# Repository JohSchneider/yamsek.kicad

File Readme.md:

Find build documentation at the Hackaday.io site for [Yet another Modular split ergonomic Keyboard](https://hackaday.io/project/21164-yamsek)

A reversible PCB for three-quarts of the keyboard matrix, with the remaining quarter being a handwired thumbcluster.

The design "fully embraces" I2C as interconnect:
- an io expander handles the matrix, the three matrix rows on the pcb, as well as the additional row in the thumbcluster
- along the edge are three places where a ribbon cable can be soldered to to connect to the next module
- "modules" are the main mcu running QMK, two of these pcbs and additional sensors (e.g. an I2C touchpad, ... )

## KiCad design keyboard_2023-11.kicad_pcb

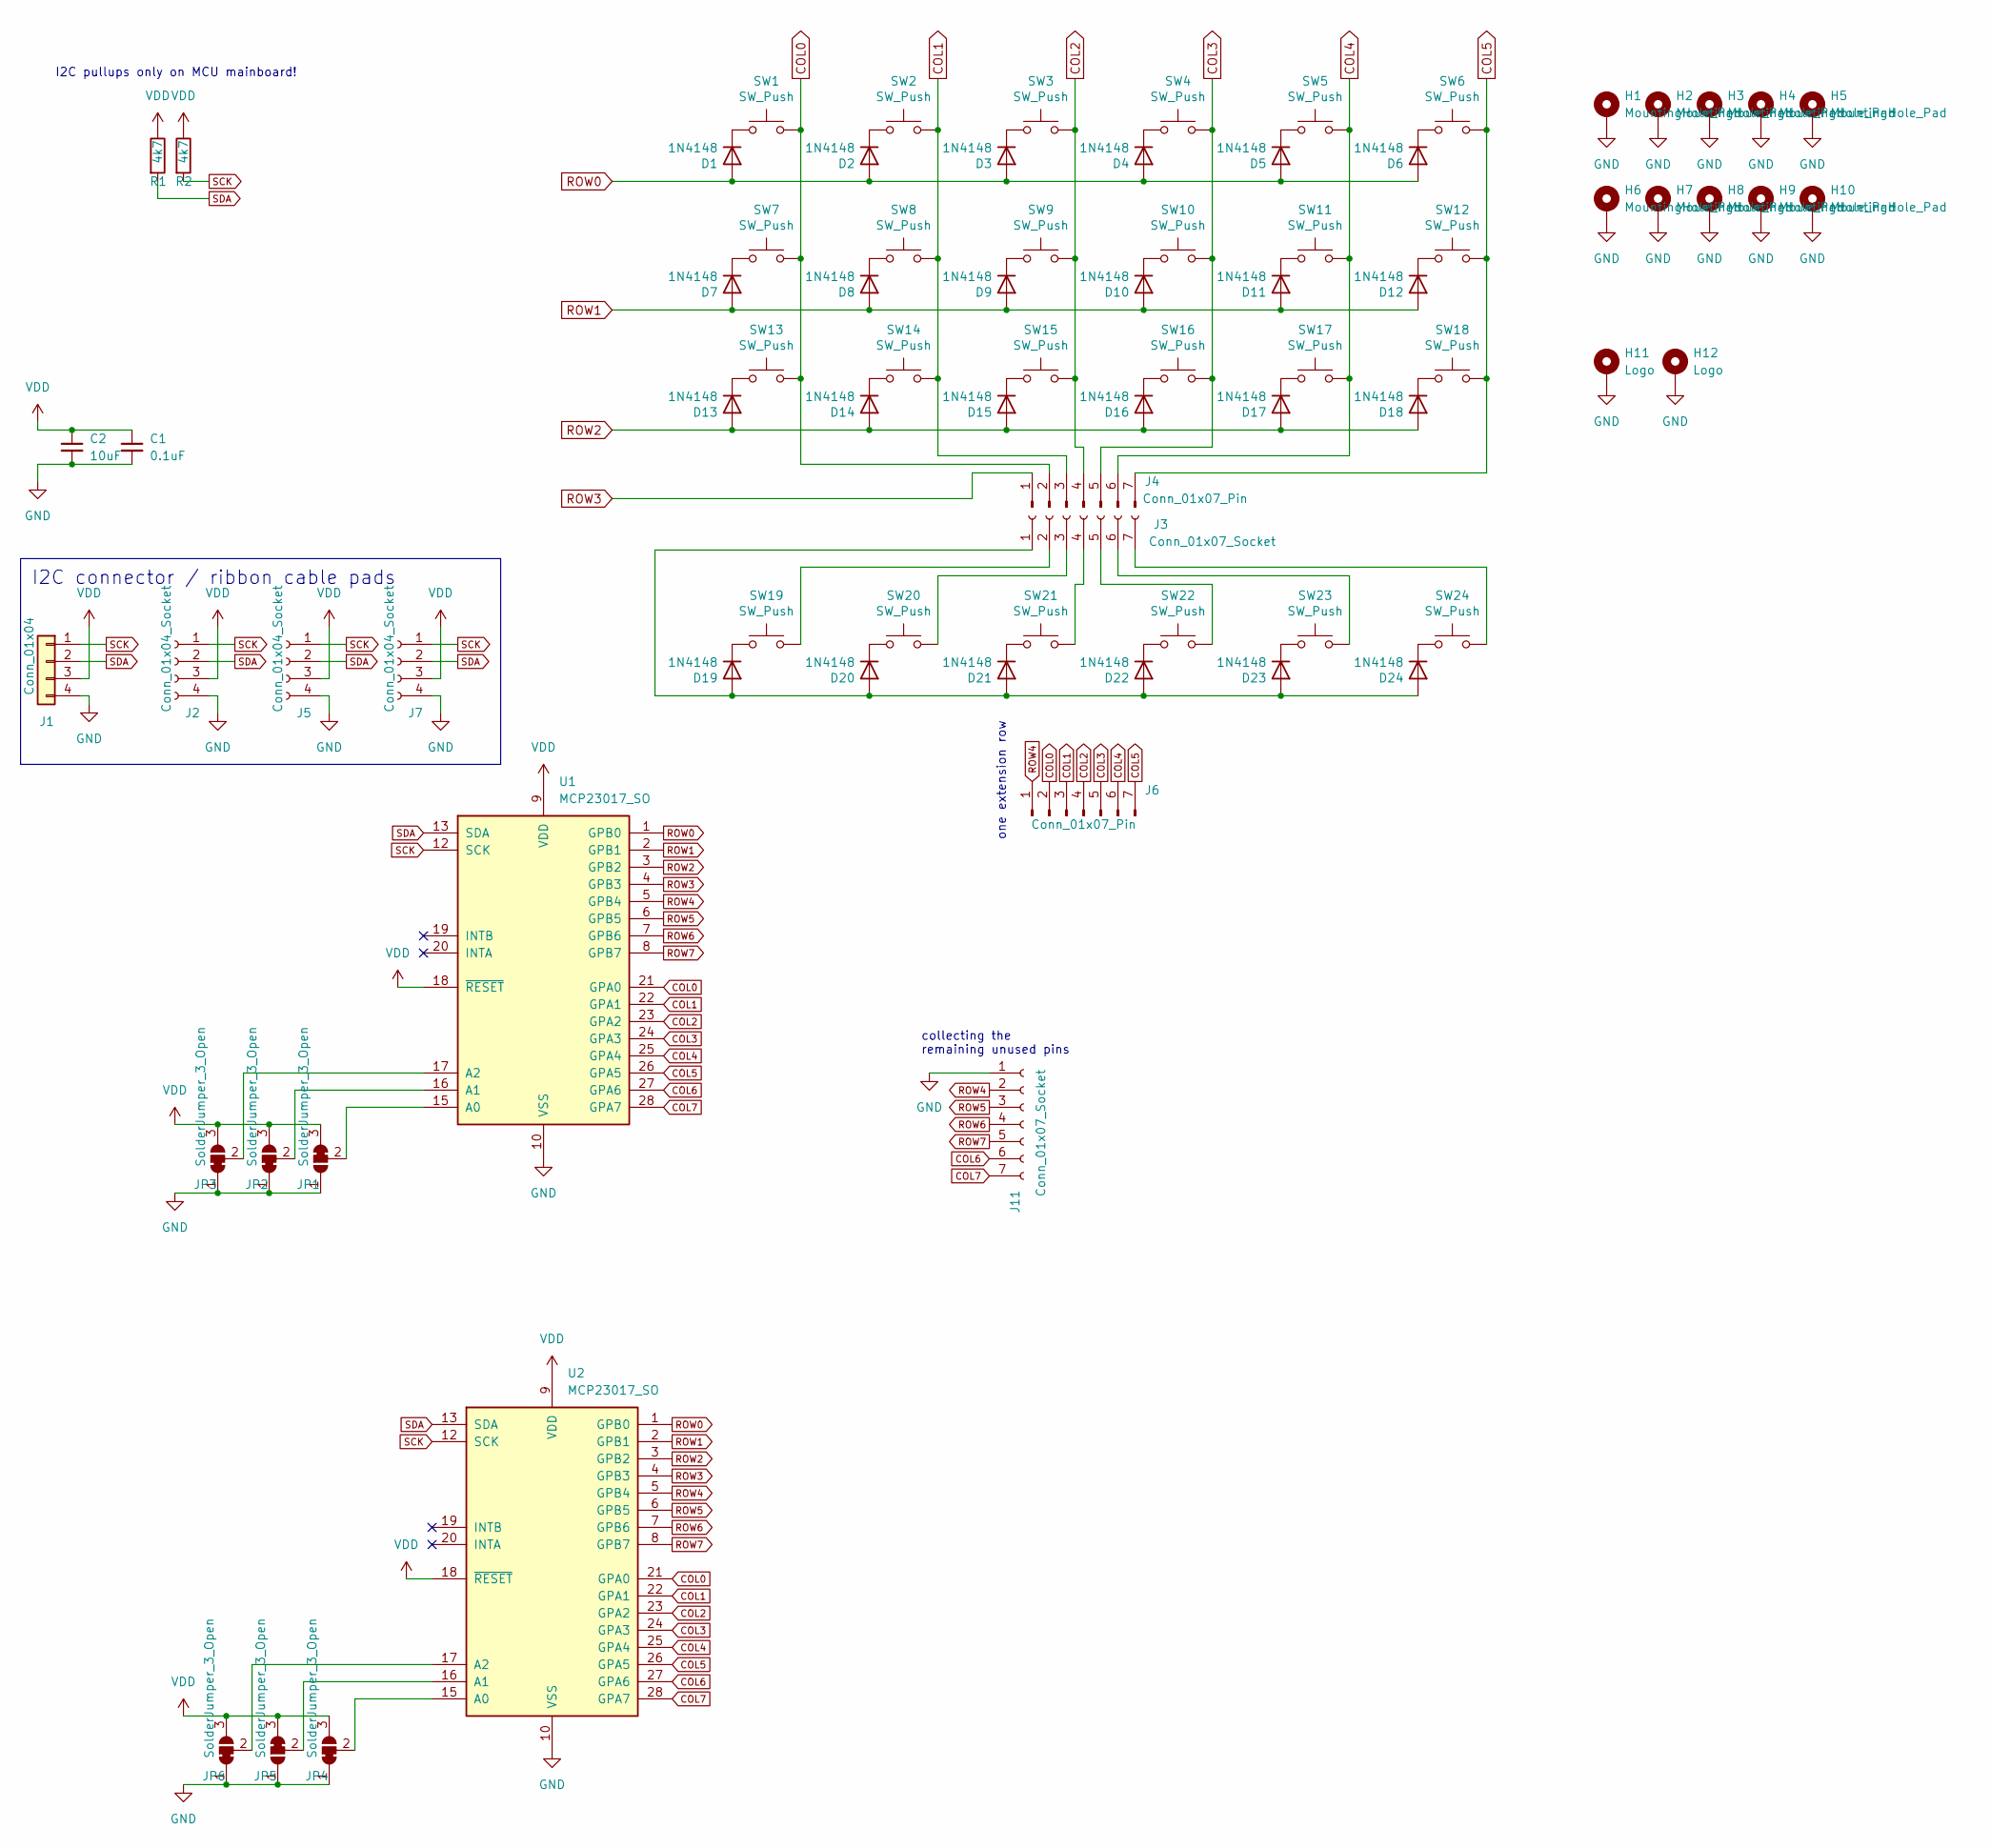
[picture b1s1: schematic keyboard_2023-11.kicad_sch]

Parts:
C1: 0.1uF; C-0805_2012Metric
C2: 10uF; C-0805_2012Metric
D1, D2, D3, D4, D5, D6, D7, D8, D9, D10, D11, D12, D13, D14, D15, D16, D17, D18, D19, D20, D21, D22, D23, D24: 1N4148; D_SOD-123
H1, H2, H3, H4, H5, H6, H7, H8, H9, H10: MountingHole_Pad; MountingHole_3.2mm_M3_Pad_Via
H11, H12: Logo; logo
J1: Conn_01x04; PinHeader_1x04_P2.54mm_Horizontal
J2, J5, J7: Conn_01x04_Socket; PinHeader_1x04_P1.27mm_Vertical
J3, J11: Conn_01x07_Socket; PinHeader_1x07_P1.27mm_Vertical
J4, J6: Conn_01x07_Pin; PinHeader_1x07_P1.27mm_Vertical
JP1, JP5: SolderJumper_3_Open; SolderJumper-3_P1.3mm_Bridged23_RoundedPad1.0x1.5mm_NumberL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
JP2, JP3, JP4, JP6: SolderJumper_3_Open; SolderJumper-3_P1.3mm_Bridged12_RoundedPad1.0x1.5mm_NumberL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
R1, R2: 4k7
SW1, SW2, SW3, SW4, SW5, SW6, SW7, SW8, SW9, SW10, SW11, SW12, SW13, SW14, SW15, SW16, SW17, SW18, SW19, SW20, SW21, SW22, SW23, SW24: SW_Push; SW_MX_reversible
U1, U2: MCP23017_SO; SOIC-28W_7.5x17.9mm_P1.27mm

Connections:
COL0: J4.2, J6.2, SW1.2, SW7.2, SW13.2, U1.21 (GPA0), U2.21 (GPA0)
COL1: J4.3, J6.3, SW2.2, SW8.2, SW14.2, U1.22 (GPA1), U2.22 (GPA1)
COL2: J4.4, J6.4, SW3.2, SW9.2, SW15.2, U1.23 (GPA2), U2.23 (GPA2)
COL3: J4.5, J6.5, SW4.2, SW10.2, SW16.2, U1.24 (GPA3), U2.24 (GPA3)
COL4: J4.6, J6.6, SW5.2, SW11.2, SW17.2, U1.25 (GPA4), U2.25 (GPA4)
COL5: J4.7, J6.7, SW6.2, SW12.2, SW18.2, U1.26 (GPA5), U2.26 (GPA5)
COL6: J11.6, U1.27 (GPA6), U2.27 (GPA6)
COL7: J11.7, U1.28 (GPA7), U2.28 (GPA7)
GND: C1.2, C2.2, H1.1, H2.1, H3.1, H4.1, H5.1, H6.1, H7.1, H8.1, H9.1, H10.1, H11.1, H12.1, J1.4, J2.4, J5.4, J7.4, J11.1, JP1.1 (A), JP2.1 (A), JP3.1 (A), JP4.1 (A), JP5.1 (A), JP6.1 (A), U1.10 (VSS), U2.10 (VSS)
unnamed: D1.1 (K), SW1.1
unnamed: D2.1 (K), SW2.1
unnamed: D3.1 (K), SW3.1
unnamed: D4.1 (K), SW4.1
unnamed: D5.1 (K), SW5.1
unnamed: D6.1 (K), SW6.1
unnamed: D7.1 (K), SW7.1
unnamed: D8.1 (K), SW8.1
unnamed: D9.1 (K), SW9.1
unnamed: D10.1 (K), SW10.1
unnamed: D11.1 (K), SW11.1
unnamed: D12.1 (K), SW12.1
unnamed: D13.1 (K), SW13.1
unnamed: D14.1 (K), SW14.1
unnamed: D15.1 (K), SW15.1
unnamed: D16.1 (K), SW16.1
unnamed: D17.1 (K), SW17.1
unnamed: D18.1 (K), SW18.1
unnamed: D19.2 (A), D20.2 (A), D21.2 (A), D22.2 (A), D23.2 (A), D24.2 (A), J3.1
unnamed: D19.1 (K), SW19.1
unnamed: D20.1 (K), SW20.1
unnamed: D21.1 (K), SW21.1
unnamed: D22.1 (K), SW22.1
unnamed: D23.1 (K), SW23.1
unnamed: D24.1 (K), SW24.1
unnamed: J3.2, SW19.2
unnamed: J3.3, SW20.2
unnamed: J3.4, SW21.2
unnamed: J3.5, SW22.2
unnamed: J3.6, SW23.2
unnamed: J3.7, SW24.2
unnamed: JP1.2 (C), U1.15 (A0)
unnamed: JP2.2 (C), U1.16 (A1)
unnamed: JP3.2 (C), U1.17 (A2)
unnamed: JP4.2 (C), U2.15 (A0)
unnamed: JP5.2 (C), U2.16 (A1)
unnamed: JP6.2 (C), U2.17 (A2)
ROW0: D1.2 (A), D2.2 (A), D3.2 (A), D4.2 (A), D5.2 (A), D6.2 (A), U1.1 (GPB0), U2.1 (GPB0)
ROW1: D7.2 (A), D8.2 (A), D9.2 (A), D10.2 (A), D11.2 (A), D12.2 (A), U1.2 (GPB1), U2.2 (GPB1)
ROW2: D13.2 (A), D14.2 (A), D15.2 (A), D16.2 (A), D17.2 (A), D18.2 (A), U1.3 (GPB2), U2.3 (GPB2)
ROW3: J4.1, U1.4 (GPB3), U2.4 (GPB3)
ROW4: J6.1, J11.2, U1.5 (GPB4), U2.5 (GPB4)
ROW5: J11.3, U1.6 (GPB5), U2.6 (GPB5)
ROW6: J11.4, U1.7 (GPB6), U2.7 (GPB6)
ROW7: J11.5, U1.8 (GPB7), U2.8 (GPB7)
SCK: J1.1, J2.1, J5.1, J7.1, R2.2, U1.12 (SCK), U2.12 (SCK)
SDA: J1.2, J2.2, J5.2, J7.2, R1.2, U1.13 (SDA), U2.13 (SDA)
VDD: C1.1, C2.1, J1.3, J2.3, J5.3, J7.3, JP1.3 (B), JP2.3 (B), JP3.3 (B), JP4.3 (B), JP5.3 (B), JP6.3 (B), R1.1, R2.1, U1.9 (VDD), U1.18 (~RESET), U2.9 (VDD), U2.18 (~RESET)

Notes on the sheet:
I2C connector / ribbon cable pads
I2C pullups only on MCU mainboard!
one extension row
collecting the remaining unused pins

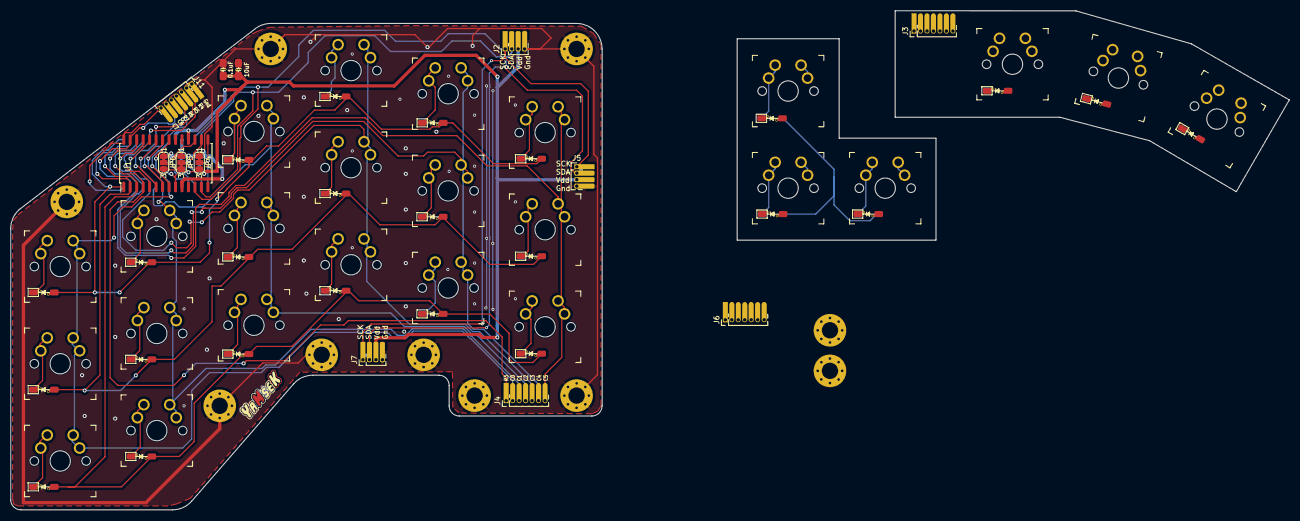
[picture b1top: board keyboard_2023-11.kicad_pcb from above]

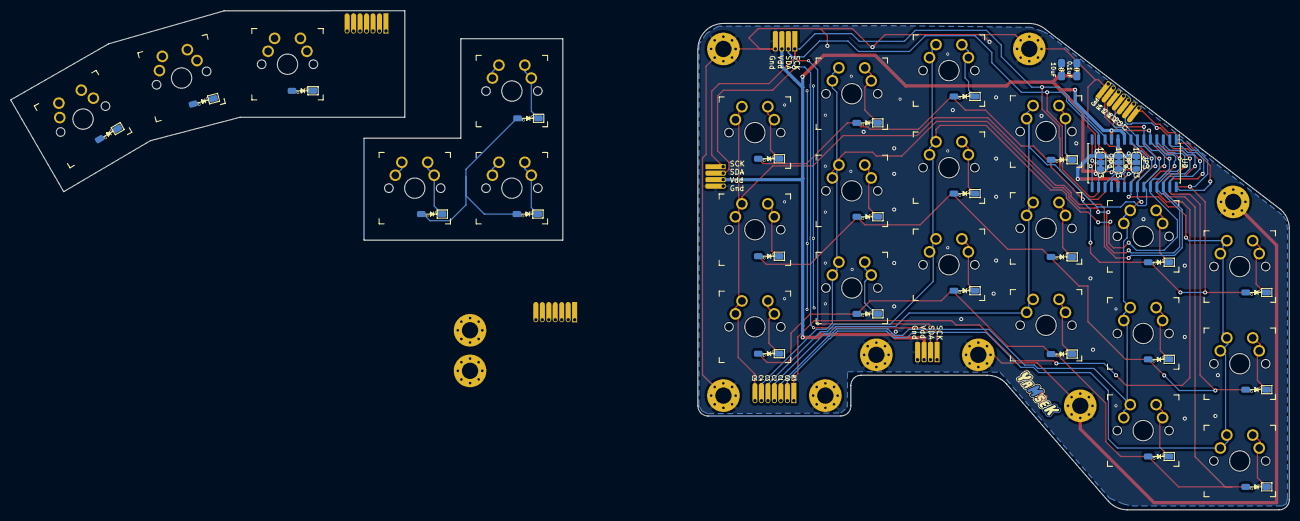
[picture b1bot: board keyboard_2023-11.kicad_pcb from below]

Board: 2 copper layers, 250.8 x 97.9 mm, 77 parts (8 on the bottom side), 57 nets.

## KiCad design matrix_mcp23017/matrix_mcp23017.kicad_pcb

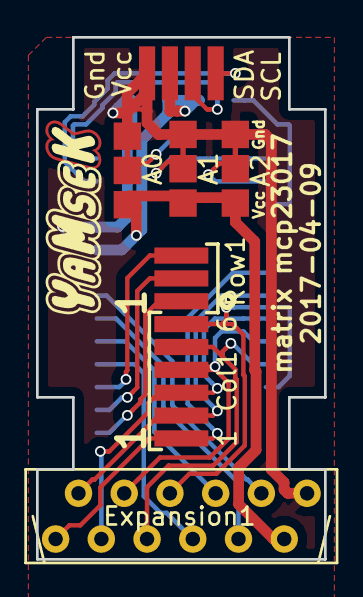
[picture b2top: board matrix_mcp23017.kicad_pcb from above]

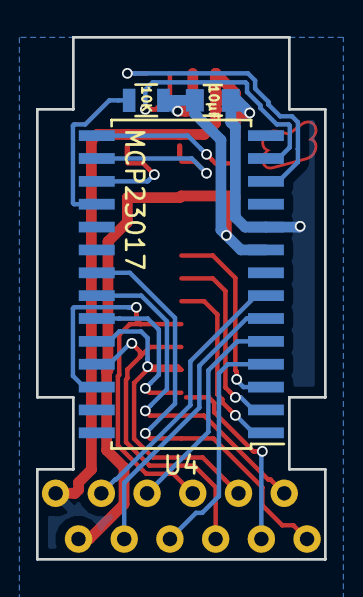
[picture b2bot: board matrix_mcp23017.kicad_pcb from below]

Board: 2 copper layers, 16.0 x 29.0 mm, 11 parts (3 on the bottom side), 21 nets.

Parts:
A0, A1, A2: address_sel; addr_jumper
C1: 10µF; C_0805
Col1: CONN_01X06; solderPads_6
Expansion1: CONN_01X12; microMatch-12_90_THT
I2C1: CONN_01X04; solderPads_4_Grove_I2C
R1: 10K; R_0805
Row1: CONN_01X03; solderPads_3
U4: MCP23017; SOIC-28W_7.5x17.9mm_Pitch1.27mm
svg2mod: G***; logo

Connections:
+5V: A0.1, A1.1, A2.1, C1.1, Expansion1.11, I2C1.3, R1.2, U4.9
/SCL: I2C1.1, U4.12
/SDA: I2C1.2, U4.13
GND: A0.3, A1.3, A2.3, C1.2, Expansion1.12, I2C1.4, U4.10
unnamed: A0.2, U4.15
unnamed: A1.2, U4.16
unnamed: A2.2, U4.17
unnamed: Col1.1, Expansion1.1, U4.21
unnamed: Col1.2, Expansion1.2, U4.22
unnamed: Col1.3, Expansion1.3, U4.23
unnamed: Col1.4, Expansion1.4, U4.24
unnamed: Col1.5, Expansion1.5, U4.25
unnamed: Col1.6, Expansion1.6, U4.26
unnamed: Expansion1.7, U4.4
unnamed: Expansion1.8, U4.5
unnamed: Expansion1.9, U4.6
unnamed: Expansion1.10, U4.7
unnamed: R1.1, U4.18
unnamed: Row1.1, U4.1
unnamed: Row1.2, U4.2
unnamed: Row1.3, U4.3

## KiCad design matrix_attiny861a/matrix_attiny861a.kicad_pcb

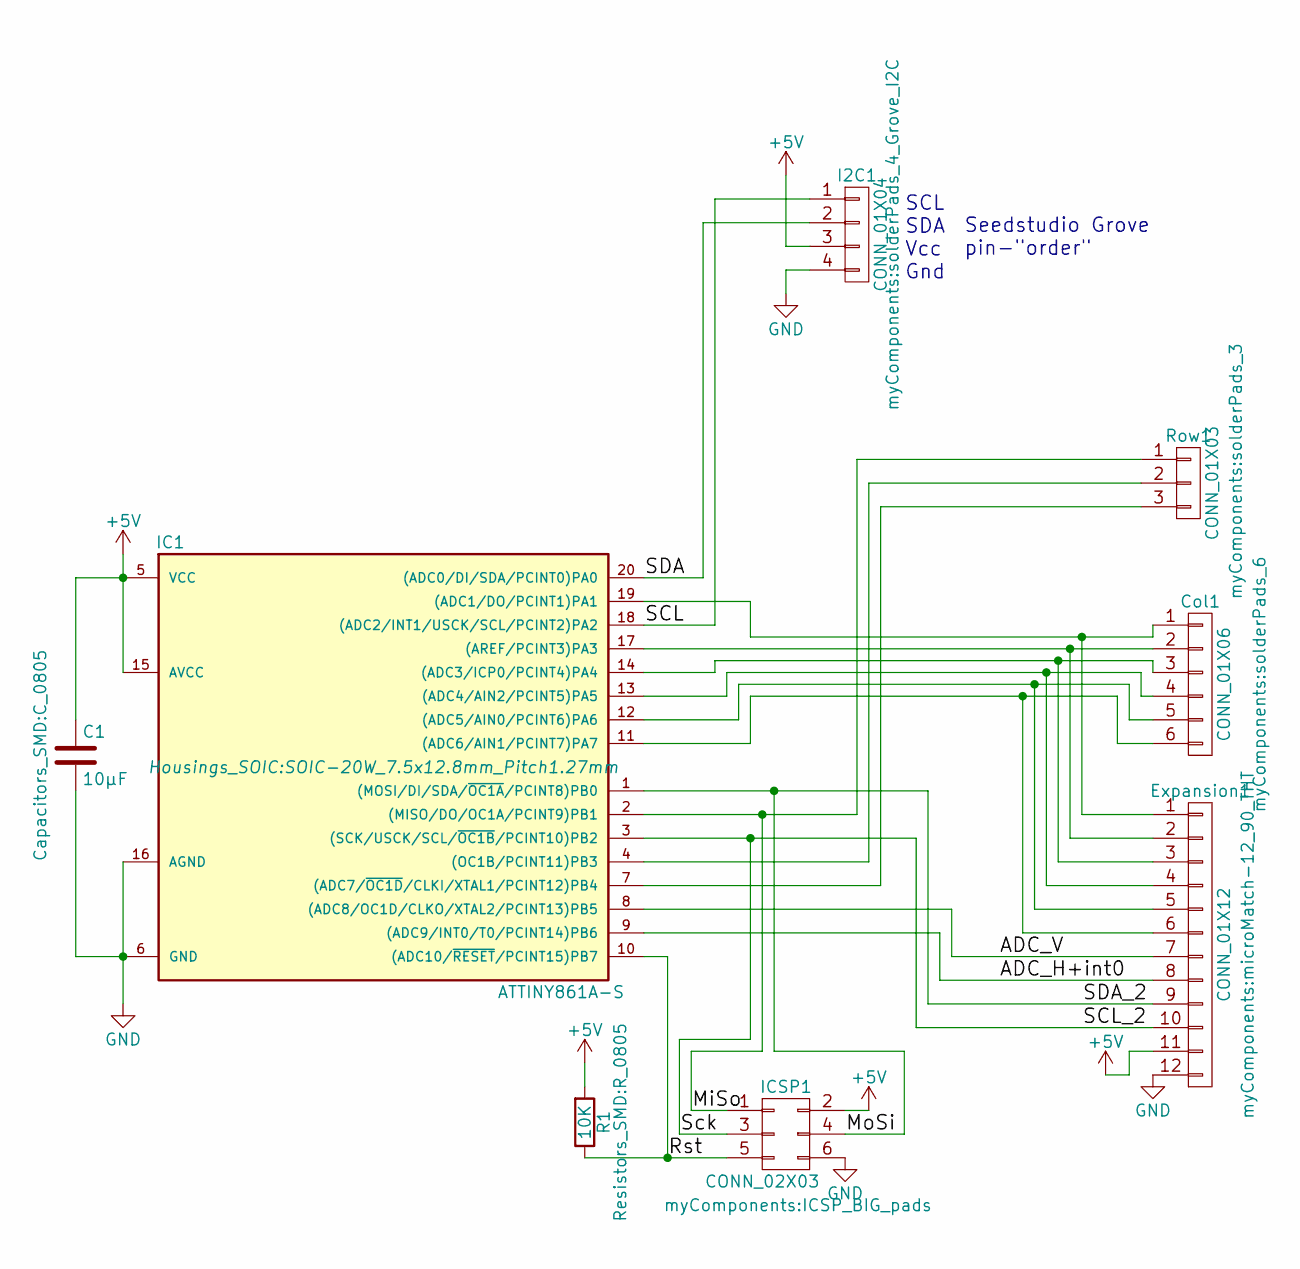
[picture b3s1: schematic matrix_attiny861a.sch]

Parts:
C1: 10µF; C_0805
Col1: CONN_01X06; solderPads_6
Expansion1: CONN_01X12; microMatch-12_90_THT
I2C1: CONN_01X04; solderPads_4_Grove_I2C
IC1: ATTINY861A-S; SOIC-20W_7.5x12.8mm_Pitch1.27mm
ICSP1: CONN_02X03; ICSP_BIG_pads
R1: 10K; R_0805
Row1: CONN_01X03; solderPads_3

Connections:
+5V: C1.1, Expansion1.11, I2C1.3, IC1.5 (VCC), IC1.15 (AVCC), ICSP1.2, R1.2
/ADC_H+int0: Expansion1.8, IC1.9 ((ADC9/INT0/T0/PCINT14)PB6)
/ADC_V: Expansion1.7, IC1.8 ((ADC8/OC1D/CLKO/XTAL2/PCINT13)PB5)
/MiSo: IC1.2 ((MISO/DO/OC1A/PCINT9)PB1), ICSP1.1, Row1.1
/MoSi: Expansion1.9, IC1.1 ((MOSI/DI/SDA/~OC1A~/PCINT8)PB0), ICSP1.4
/Rst: IC1.10 ((ADC10/~RESET~/PCINT15)PB7), ICSP1.5, R1.1
/SCL: I2C1.1, IC1.18 ((ADC2/INT1/USCK/SCL/PCINT2)PA2)
/SCL_2: Expansion1.10, IC1.3 ((SCK/USCK/SCL/~OC1B~/PCINT10)PB2), ICSP1.3
/SDA: I2C1.2, IC1.20 ((ADC0/DI/SDA/PCINT0)PA0)
GND: C1.2, Expansion1.12, I2C1.4, IC1.6 (GND), IC1.16 (AGND), ICSP1.6
unnamed: Col1.1, Expansion1.1, IC1.19 ((ADC1/DO/PCINT1)PA1)
unnamed: Col1.2, Expansion1.2, IC1.17 ((AREF/PCINT3)PA3)
unnamed: Col1.3, Expansion1.3, IC1.14 ((ADC3/ICP0/PCINT4)PA4)
unnamed: Col1.4, Expansion1.4, IC1.13 ((ADC4/AIN2/PCINT5)PA5)
unnamed: Col1.5, Expansion1.5, IC1.12 ((ADC5/AIN0/PCINT6)PA6)
unnamed: Col1.6, Expansion1.6, IC1.11 ((ADC6/AIN1/PCINT7)PA7)
unnamed: IC1.4 ((OC1B/PCINT11)PB3), Row1.2
unnamed: IC1.7 ((ADC7/~OC1D~/CLKI/XTAL1/PCINT12)PB4), Row1.3

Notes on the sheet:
SCL SDA Vcc Gnd
Seedstudio Grove pin-"order"

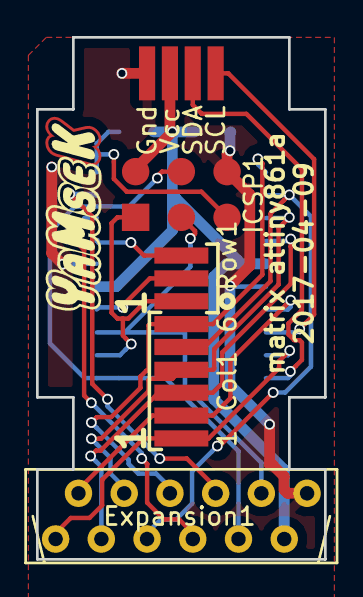
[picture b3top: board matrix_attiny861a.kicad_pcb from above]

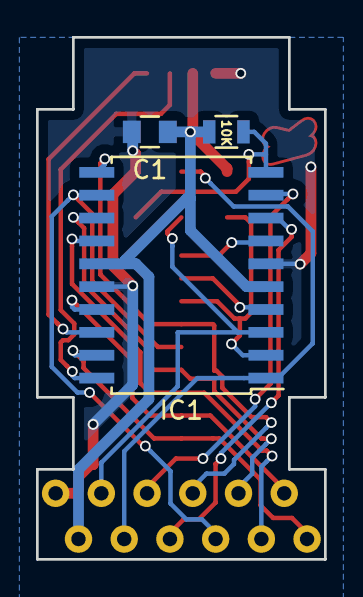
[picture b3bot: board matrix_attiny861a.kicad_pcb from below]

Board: 2 copper layers, 16.0 x 29.0 mm, 9 parts (3 on the bottom side), 18 nets.

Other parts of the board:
svg2mod: G***; logo

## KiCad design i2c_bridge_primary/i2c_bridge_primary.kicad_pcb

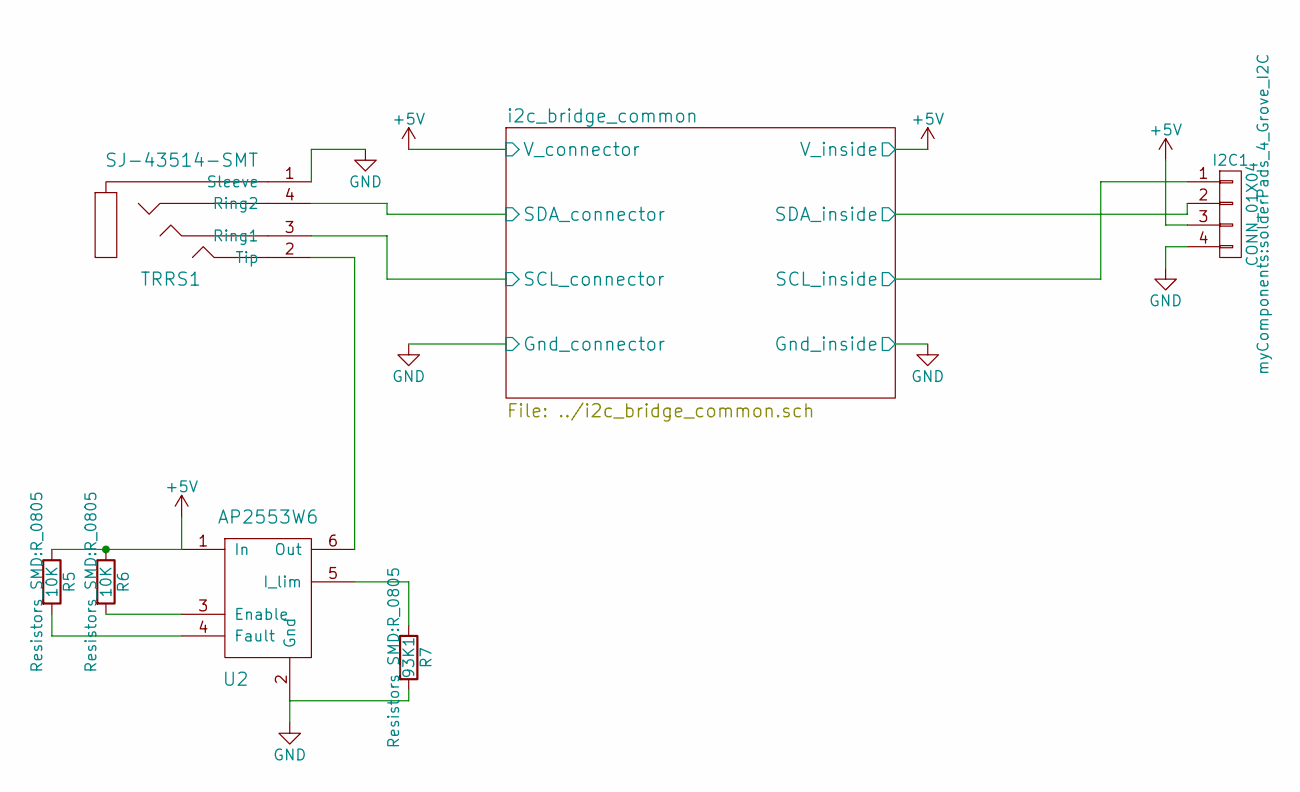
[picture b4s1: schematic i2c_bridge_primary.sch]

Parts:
I2C1: CONN_01X04; solderPads_4_Grove_I2C
R5, R6: 10K; R_0805
R7: 93K1; R_0805
TRRS1: SJ-43514-SMT; audio_smd_SJ-43514-SMT
U2: AP2553W6; SOT-23-6_Handsoldering

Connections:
+5V: I2C1.3, R5.1, R6.1, U2.1 (In); also elsewhere on the board
/i2c_bridge_common/SCL_connector: TRRS1.3 (Ring1); also elsewhere on the board
/i2c_bridge_common/SCL_inside: I2C1.1; also elsewhere on the board
/i2c_bridge_common/SDA_connector: TRRS1.4 (Ring2); also elsewhere on the board
/i2c_bridge_common/SDA_inside: I2C1.2; also elsewhere on the board
GND: I2C1.4, R7.2, TRRS1.1 (Sleeve), U2.2 (Gnd); also elsewhere on the board
unnamed: R5.2, U2.4 (Fault)
unnamed: R6.2, U2.3 (Enable)
unnamed: R7.1, U2.5 (I_lim)
unnamed: TRRS1.2 (Tip), U2.6 (Out)

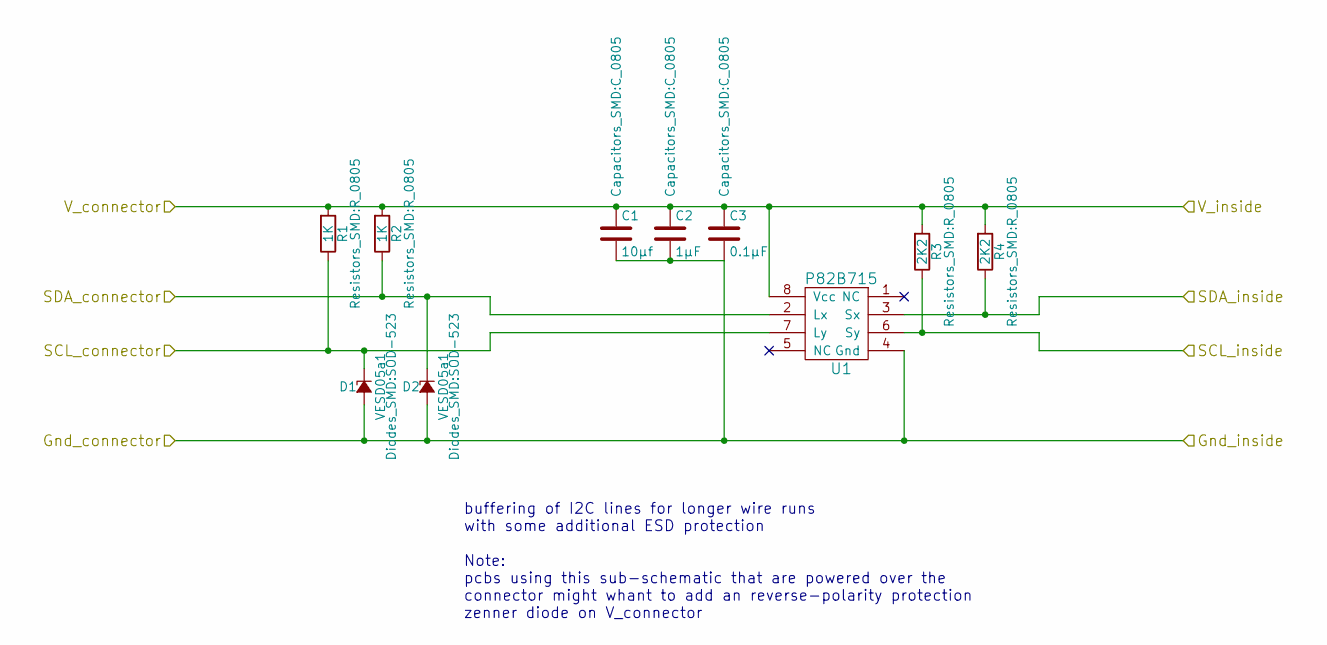
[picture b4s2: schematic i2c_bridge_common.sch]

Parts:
C1: 10µf; C_0805
C2: 1µF; C_0805
C3: 0.1µF; C_0805
D1, D2: VESD05a1; SOD-523
R1, R2: 1K; R_0805
R3, R4: 2K2; R_0805
U1: P82B715; SOIC-8-N

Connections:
+5V: C1.1, C2.1, C3.1, R1.2, R2.2, R3.2, R4.2, U1.8 (Vcc); also elsewhere on the board
/i2c_bridge_common/SCL_connector: D1.1 (K), R1.1, U1.7 (Ly); also elsewhere on the board
/i2c_bridge_common/SCL_inside: R3.1, U1.6 (Sy); also elsewhere on the board
/i2c_bridge_common/SDA_connector: D2.1 (K), R2.1, U1.2 (Lx); also elsewhere on the board
/i2c_bridge_common/SDA_inside: R4.1, U1.3 (Sx); also elsewhere on the board
GND: C1.2, C2.2, C3.2, D1.2 (A), D2.2 (A), U1.4 (Gnd); also elsewhere on the board

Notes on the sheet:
buffering of I2C lines for longer wire runs with some additional ESD protection Note: pcbs using this sub-schematic that are powered over the connector might whant to add an reverse-polarity protection zenner diode on V_connector

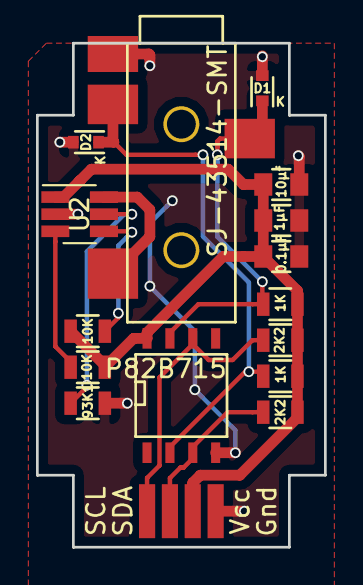
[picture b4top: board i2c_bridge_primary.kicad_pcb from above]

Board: 2 copper layers, 16.0 x 28.0 mm, 17 parts (1 on the bottom side), 10 nets.

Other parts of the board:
svg2mod: G***; logo

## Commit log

2017-04-07 version control the growinb board family
2017-04-07 single board slave for the attiny was phased out in favour of split slave+breakout scheme
2017-04-07 more spacious slave design, matching the main-power board outline
2017-04-07 added pcb baks to ignore
2017-04-07 bugfixing
2017-04-08 switched reset pullups from 2K2 to 10K
2017-04-08 more fixes :-s
2017-04-09 move to a more consistens nameing scheme
    matrix_ parts denote breakout boards that directly connect to the keyboard
    matrix
    i2c_bridge are boards connecting to each other via external connectors (TRRS at
    the moment) and handle i2c buffering, ESD protection, current limiting (primary)
    and reverse polarity protection (secondary)
2017-04-09 rename of i2c_bridge_common
2017-04-09 added YamseK logo :-)
2017-04-09 tweaks to the logo
2017-04-09 bugfixes preparing first order to oshpark
2017-04-13 prepared logo for blenders svg import
2017-04-27 added pin-1 marking on back silkscreen for the MCP23017
2017-05-01 removed missing "-rescue" lib
    where did it come from and what was it for?
2017-05-27 updated readme with link to hackaday.io project site
2023-12-03 snapshot
2023-12-03 PCB: move ioexpander from right-edge to up-left corner
    removing/shuffeling mounting holes, to remove pcb area that might interfere with monoblock design; or possibly with electronics placed between the two halves
2023-12-03 routed 90%
2023-12-04 fix solder jumpers
    front/back io-expander need sepparate jumpers, as the already have preset values which might conflict with user selection = create a short.
    switch solder jumpers to opposite side of board of the coresponding io-expander
2023-12-07 ready for ORDER
2023-12-15 better solder jumpers?
    adding a solder mask cutout where the pads are default-connected, to better see which part needs to be scrached out
2023-12-19 closing gapts:
    noticed a gap on the manufactured pcb between index and middlefinger columns
    => shifted evertything a milimeter closer together
2023-12-23 moved column 3 1mm down
    added thumbcluster "port" (draft)
2023-12-24 V2: gerber 2 JLCPCB
    additional i2c ports
    mounting "tab" for thumb cluster
    nudged rows 3 (ringfinter) and 4 (middlefinger) a bit down
2024-01-11 remove wrong 'C7' from silkscreen labels
2024-01-11 c-numbering from 0 for columns&rows
    to better align with the firmware, count from 0 instead of from 1
2024-01-11 add Readme.md
2024-01-11 cleanup schematic for release
2024-01-11 add pcb-render to Readme
2024-01-11 Update Readme.md
    with more pictures
